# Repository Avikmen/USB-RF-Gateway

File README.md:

## USB RF Gateway on NRF24L01 or RFM69

  This is my mini project on STM32. Many makers use low cost radio transmitters NRF24L01 and RFM69 in their projects. This PCB should facilitate the use of radio modules for use as transmitters in USB devices. Can also be used as a RF-dongle for Raspberry Pi. 
  The basis of the device is the microcontroller STM32F042G6U6 in the case UFQFPN28 4x4 mm (smallest footprint controller enclosure I found on sale). 
  It is possible to download .bin files directly via USB, thanks to the built-in bootloader. For the whole, you’ll need to connect device in USB port on while holding down the “BOOT” button. I used STM32CubeProgrammer to download .bin file. 6-pin SWD Tag-Connect is also available for debugging.

You can place the programmed and debugged device in the enclosure of Gainta G1901G or G1901C. I specifically tried to develop this device for such cases, because they are quite cheap and universal.

### Features

- NRF24L01 SMD
- RFM69 868 or 915 MHz (to minimize antenna size, compared to antenna sizes for 433MHz)
- No programming probe needed for uploading firmware
- Tag-Connect for debugging
- Debugging LED on board
- USB port ESD protection
- The NRF24L01 *(not tested RFM69 version)* version is perfect for the Gainta G1901C or 1901G enclosure (if you use a USB connector for deep PCB landing)

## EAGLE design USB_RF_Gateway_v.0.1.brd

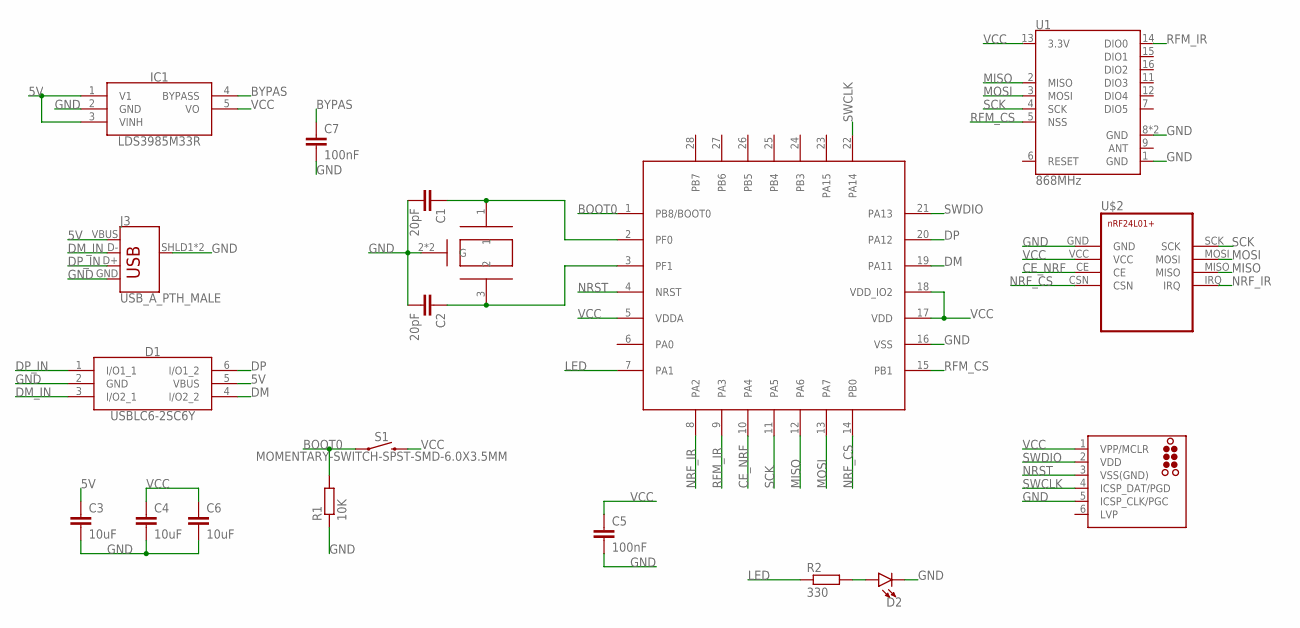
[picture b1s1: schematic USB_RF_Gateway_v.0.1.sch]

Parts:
C1, C2: 20pF; C0603
C3, C4, C6: 10uF; C0805
C5, C7: 100nF; C0603
D1: USBLC6-2SC6Y; SOT95P280X145-6N
D2: LED0603; LED-0603
IC1: LDS3985M33R; SOT95P280X145-5N
J2: TC2030-MCP-NL
J3: USB_A_PTH_MALE; USB-A-H
R1: 10K; R0603
R2: 330; R0603
S1: MOMENTARY-SWITCH-SPST-SMD-6.0X3.5MM; TACTILE_SWITCH_SMD_6.0X3.5MM
U1: 868MHz; RFM69HCW-XXXS2
U$1: ECS-160-12-37B-CTN-TR; ECS-160-12-37B-CTN
U$2: NRF24L01+NRF24L01+MINI; NRF24L01+MINI
U$3: STMF042G6U6; STM32F042_UFQPN28_4X4MM

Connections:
5V: C3.1, D1.5 (VBUS), IC1.1 (V1), IC1.3 (VINH), J3.VBUS
BOOT0: R1.2, S1.1, U$3.1 (PB8/BOOT0)
BYPAS: C7.1, IC1.4 (BYPASS)
CE_NRF: U$2.CE, U$3.10 (PA4)
DM: D1.4 (I/O2_2), U$3.19 (PA11)
DM_IN: D1.3 (I/O2_1), J3.D-
DP: D1.6 (I/O1_2), U$3.20 (PA12)
DP_IN: D1.1 (I/O1_1), J3.D+
GND: C1.2, C2.2, C3.2, C4.2, C5.2, C6.2, C7.2, D1.2 (GND), D2.C, IC1.2 (GND), J2.5 (ICSP_CLK/PGC), J3.GND, J3.SHLD1 (SHIELD), J3.SHLD2 (SHIELD), R1.1, U1.1 (GND), U1.8 (GND), U1.10 (GND), U$1.2 (G), U$1.4 (G), U$2.GND, U$3.16 (VSS)
LED: R2.1, U$3.7 (PA1)
MISO: U1.2 (MISO), U$2.MISO, U$3.12 (PA6)
MOSI: U1.3 (MOSI), U$2.MOSI, U$3.13 (PA7)
unnamed: C1.1, U$1.1, U$3.2 (PF0)
unnamed: C2.1, U$1.3 (2), U$3.3 (PF1)
unnamed: D2.A, R2.2
NRF_CS: U$2.CSN, U$3.14 (PB0)
NRF_IR: U$2.IRQ, U$3.8 (PA2)
NRST: J2.3 (VSS(GND)), U$3.4 (NRST)
RFM_CS: U1.5 (NSS), U$3.15 (PB1)
RFM_IR: U1.14 (DIO0), U$3.9 (PA3)
SCK: U1.4 (SCK), U$2.SCK, U$3.11 (PA5)
SWCLK: J2.4 (ICSP_DAT/PGD), U$3.22 (PA14)
SWDIO: J2.2 (VDD), U$3.21 (PA13)
VCC: C4.1, C5.1, C6.1, IC1.5 (VO), J2.1 (VPP/MCLR), S1.2, U1.13 (3.3V), U$2.VCC, U$3.5 (VDDA), U$3.17 (VDD), U$3.18 (VDD_IO2)

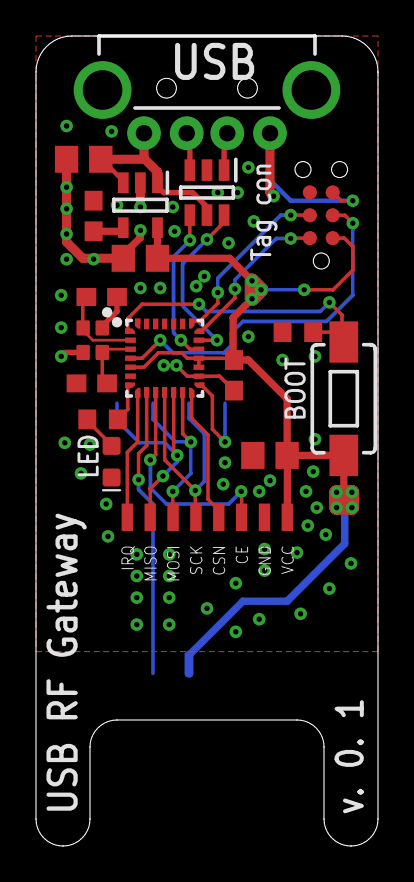
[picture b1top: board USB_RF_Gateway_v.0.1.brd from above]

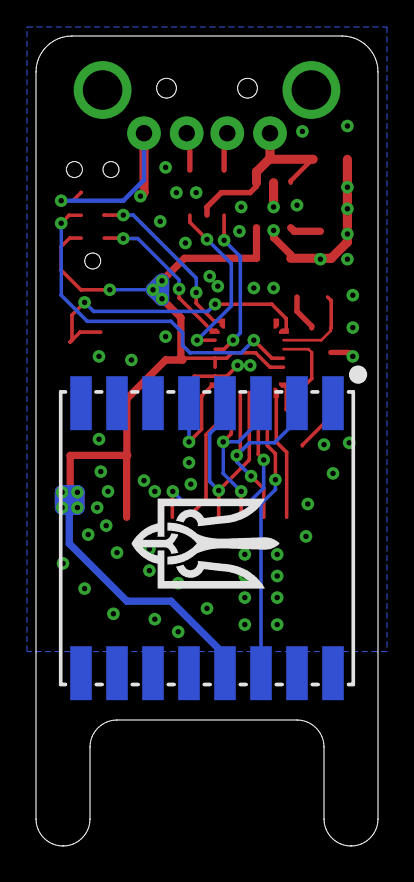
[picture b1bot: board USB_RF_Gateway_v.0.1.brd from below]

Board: 2 copper layers, 19.0 x 45.0 mm, 20 parts (2 on the bottom side), 24 nets.

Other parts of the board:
U$4: GERB_5MM

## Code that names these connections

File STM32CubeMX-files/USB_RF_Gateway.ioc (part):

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Mcu.Name=STM32F042G(4-6)Ux
Mcu.Package=UFQFPN28
Mcu.UserName=STM32F042G6Ux
PA1.GPIOParameters=GPIO_Label
PA1.GPIO_Label=LED
PA1.Signal=GPIO_Output
PA11.Mode=Device
PA11.Signal=USB_DM
PA12.Mode=Device
PA12.Signal=USB_DP
PA13.Mode=Serial_Wire
PA13.Signal=SYS_SWDIO
PA14.Mode=Serial_Wire
PA14.Signal=SYS_SWCLK
PA2.GPIOParameters=GPIO_Label
PA2.GPIO_Label=NRF_IR
PA2.Signal=GPXTI2
PA3.GPIOParameters=GPIO_Label
PA3.GPIO_Label=RFM_IR
PA3.Signal=GPXTI3
PA4.GPIOParameters=GPIO_Label
PA4.GPIO_Label=CE_NRF
PA4.Signal=GPIO_Output
PA5.Mode=Full_Duplex_Master
PA5.Signal=SPI1_SCK
PA6.Mode=Full_Duplex_Master
PA6.Signal=SPI1_MISO
PA7.Mode=Full_Duplex_Master
PA7.Signal=SPI1_MOSI
PB0.GPIOParameters=GPIO_Label
PB0.GPIO_Label=NRF_CS
PB0.Signal=GPIO_Output
PB1.GPIOParameters=GPIO_Label
PB1.GPIO_Label=RFM_CS
PB1.Signal=GPIO_Output
PF0-OSC_IN.Mode=HSE-External-Oscillator
PF0-OSC_IN.Signal=RCC_OSC_IN
PF1-OSC_OUT.Mode=HSE-External-Oscillator
PF1-OSC_OUT.Signal=RCC_OSC_OUT
RCC.HSE_VALUE=16000000
RCC.SYSCLKFreq_VALUE=32000000
RCC.SYSCLKSource=RCC_SYSCLKSOURCE_PLLCLK
board=custom

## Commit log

2019-08-24 Set theme jekyll-theme-cayman
2019-08-24 Update ReadMe file
2019-08-24 Add device photos
2019-08-24 Add photo to ReadMe
2019-08-24 Update images
2019-08-24 Update Features
2019-09-06 Photos of the enclosure G1901C added
2020-02-06 Update README.md
    Added button to buy on Tindie store

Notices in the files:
parts and their libraries:
SparkFun-Connectors: Licensing: Creative Commons ShareAlike 4.0 International - https://creativecommons.org/licenses/by-sa/4.0
tag-connect: ©2009 ROFA.cz - modified and updated by Robert Darlington ‹rdarlington@gmail.com›
